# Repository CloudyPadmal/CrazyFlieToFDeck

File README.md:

# CrazyFlieToFDeck

This repository contains KiCAD source files and generated gerber files for **CrazyFlie Obstacle Avoidance Sensor Deck**.

<table>
<tr>
<th>Front View</td>
<th>Bottom View</td>
</tr>
<tr>
<td></td>
<td></td>
</tr>
</table>

## Time of Flight Sensor

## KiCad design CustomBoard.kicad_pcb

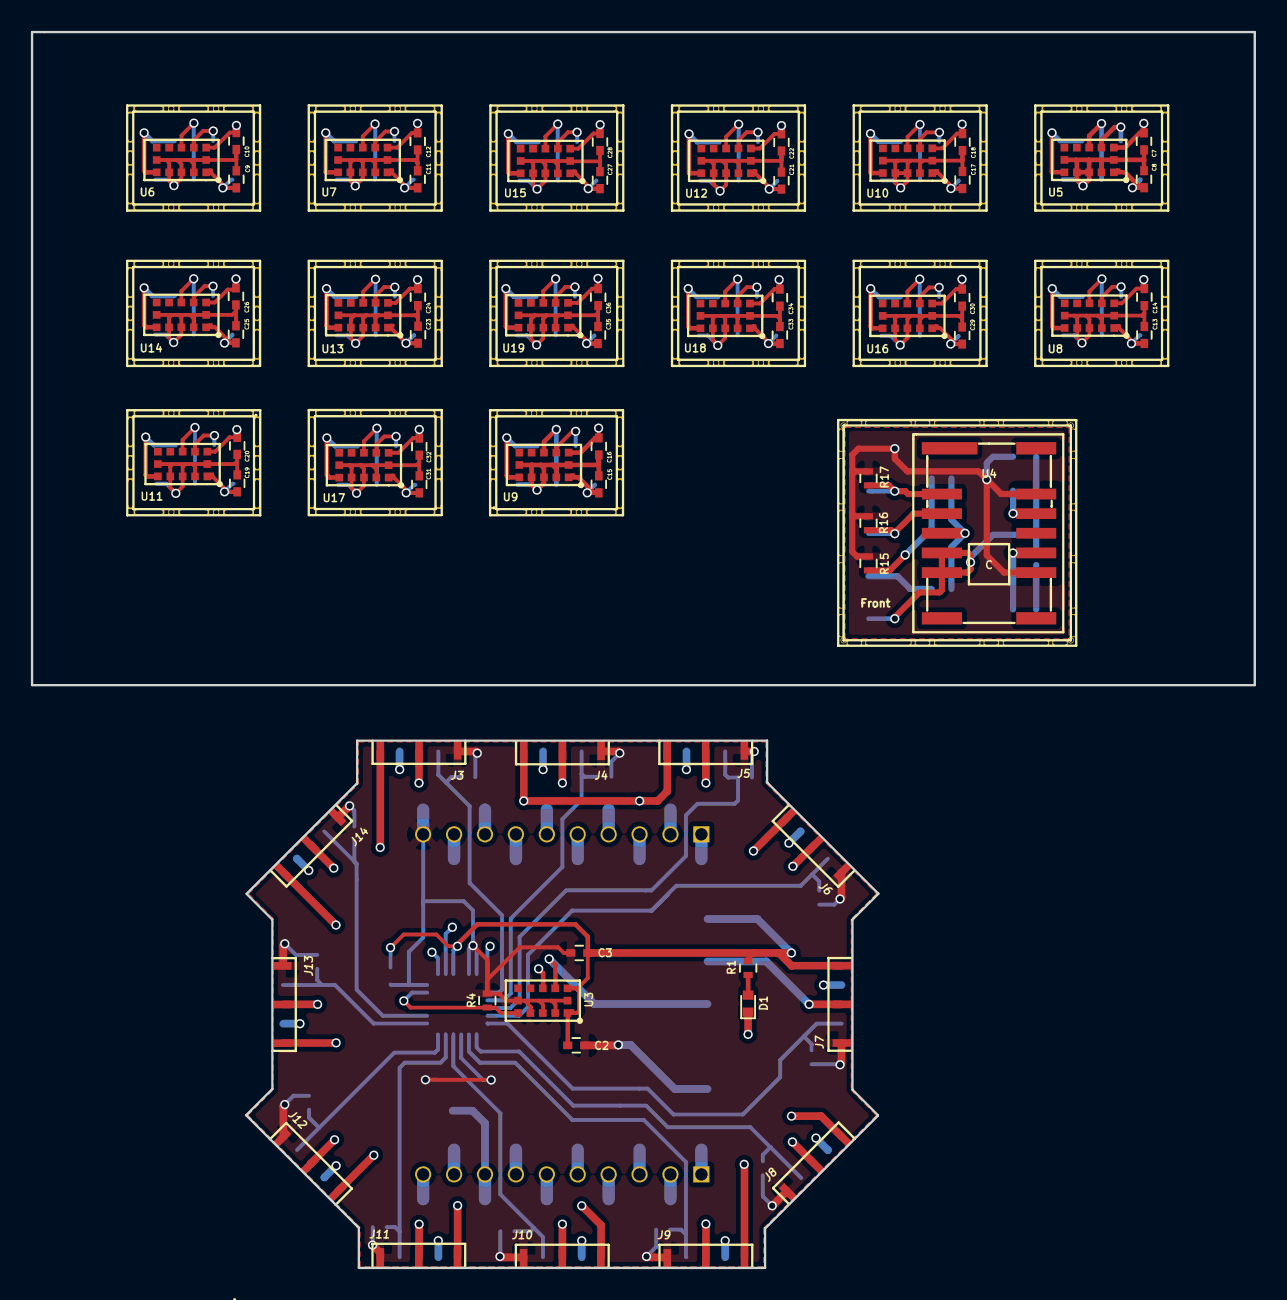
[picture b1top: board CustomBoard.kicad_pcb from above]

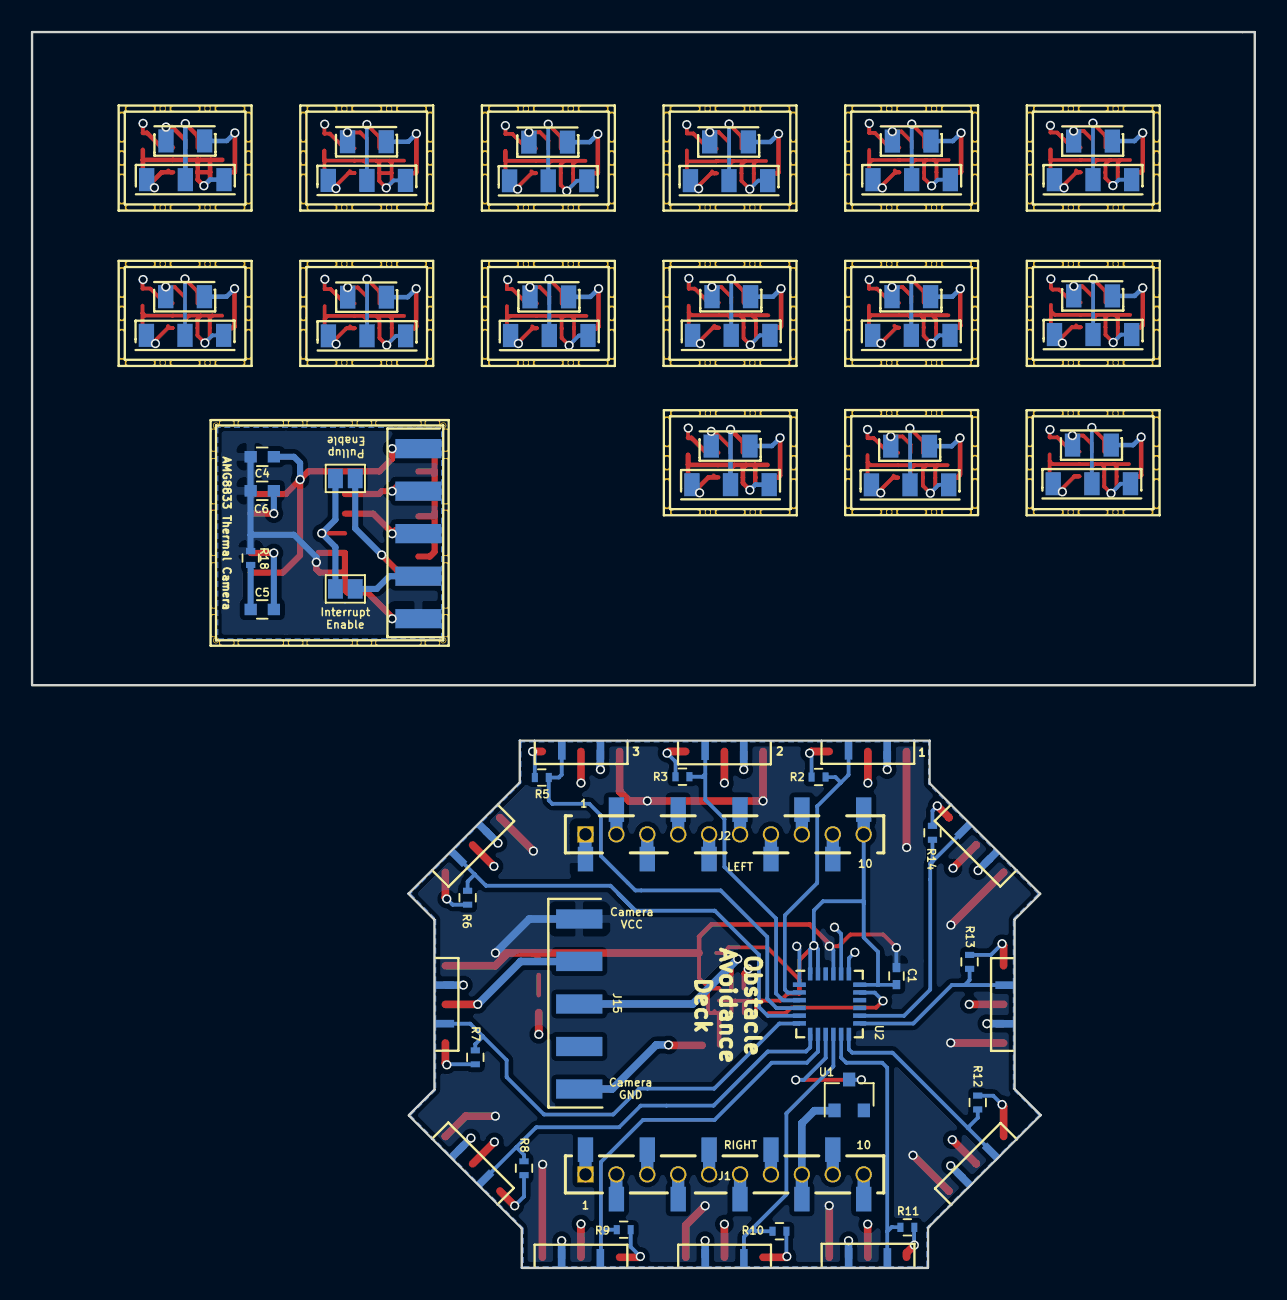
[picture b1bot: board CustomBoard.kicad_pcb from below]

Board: 4 copper layers, 79.1 x 79.9 mm, 122 parts (55 on the bottom side), 105 nets.

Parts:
C1, C2, C7, C9, C11, C13, C15, C17, C19, C21, C23, C25, C27, C29, C31, C33, C35: 100n; C_0402
C3, C8, C10, C12, C14, C16, C18, C20, C22, C24, C26, C28, C30, C32, C34, C36: 4.7u; C_0402
C4: 10u; C_0603
C5: 1u; C_0603
C6: 1.5u; C_0603
D1: POWER_LED; LED_0402
J1: RIGHT; BF090-10-X-B2
J2: LEFT; BF090-10-X-B2
J3: Sensor01; SensorPads
J4: Sensor02; SensorPads
J5: Sensor03; SensorPads
J6: Sensor04; SensorPads
J7: Sensor05; SensorPads
J8: Sensor06; SensorPads
J9: Sensor07; SensorPads
J10: Sensor08; SensorPads
J11: Sensor09; SensorPads
J12: Sensor10; SensorPads
J13: Sensor11; SensorPads
J14: Sensor12; SensorPads
J15, J18: Camera; AMGCam
J16: PulCon; GS2
J17: IntCon; GS2
J19, J21, J23, J25, J27, J29, J31, J33, J35, J37, J39, J41, J43, J45, J47: Top; ToFTop
J20, J22, J24, J26, J28, J30, J32, J34, J36, J38, J40, J42, J44, J46, J48: Bot; ToFBottom
R1: 2k; R_0402
R2, R3, R4, R5, R6, R7, R8, R9, R10, R11, R12, R13, R14, R15, R16, R17: 10k; R_0402
R18: 20R; R_0402
U1: DS28E05; SOT-23
U2: PCA9555; QFN-24_4x4mm_Pitch0.5mm
U3, U5, U6, U7, U8, U9, U10, U11, U12, U13, U14, U15, U16, U17, U18, U19: VL53L1X
U4: AMG8833

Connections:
GND: C1.2, C2.2, C3.2, J2.10, J3.1, J4.1, J5.1, J6.1, J7.1, J8.1, J9.1, J10.1, J11.1, J12.1, J13.1, J14.1, J15.1, R2.1, R3.1, R4.2, R5.1, R6.1, R7.1, R8.1, R9.1, R10.1, R11.1, R12.1, R13.1, R14.1, U1.3, U2.9, U2.18, U2.23, U2.24, U3.2, U3.3, U3.4, U3.6, U3.12
GNDCam: C4.2, C6.2, J18.1, R18.2, U4.5, U4.6
INTCam: J17.2, J18.2
unnamed: C5.1, U4.10
unnamed: C5.2, R18.1
unnamed: C6.1, U4.12
unnamed: C7.1, C8.1, J20.1, U5.1, U5.11
unnamed: C7.2, C8.2, J20.3, U5.2, U5.3, U5.4, U5.6, U5.12
unnamed: C9.1, C10.1, J22.1, U6.1, U6.11
unnamed: C9.2, C10.2, J22.3, U6.2, U6.3, U6.4, U6.6, U6.12
unnamed: C11.1, C12.1, J24.1, U7.1, U7.11
unnamed: C11.2, C12.2, J24.3, U7.2, U7.3, U7.4, U7.6, U7.12
unnamed: C13.1, C14.1, J26.1, U8.1, U8.11
unnamed: C13.2, C14.2, J26.3, U8.2, U8.3, U8.4, U8.6, U8.12
unnamed: C15.1, C16.1, J28.1, U9.1, U9.11
unnamed: C15.2, C16.2, J28.3, U9.2, U9.3, U9.4, U9.6, U9.12
unnamed: C17.1, C18.1, J30.1, U10.1, U10.11
unnamed: C17.2, C18.2, J30.3, U10.2, U10.3, U10.4, U10.6, U10.12
unnamed: C19.1, C20.1, J32.1, U11.1, U11.11
unnamed: C19.2, C20.2, J32.3, U11.2, U11.3, U11.4, U11.6, U11.12
unnamed: C21.1, C22.1, J34.1, U12.1, U12.11
unnamed: C21.2, C22.2, J34.3, U12.2, U12.3, U12.4, U12.6, U12.12
unnamed: C23.1, C24.1, J36.1, U13.1, U13.11
unnamed: C23.2, C24.2, J36.3, U13.2, U13.3, U13.4, U13.6, U13.12
unnamed: C25.1, C26.1, J38.1, U14.1, U14.11
unnamed: C25.2, C26.2, J38.3, U14.2, U14.3, U14.4, U14.6, U14.12
unnamed: C27.1, C28.1, J40.1, U15.1, U15.11
unnamed: C27.2, C28.2, J40.3, U15.2, U15.3, U15.4, U15.6, U15.12
unnamed: C29.1, C30.1, J42.1, U16.1, U16.11
unnamed: C29.2, C30.2, J42.3, U16.2, U16.3, U16.4, U16.6, U16.12
unnamed: C31.1, C32.1, J44.1, U17.1, U17.11
unnamed: C31.2, C32.2, J44.3, U17.2, U17.3, U17.4, U17.6, U17.12
unnamed: C33.1, C34.1, J46.1, U18.1, U18.11
unnamed: C33.2, C34.2, J46.3, U18.2, U18.3, U18.4, U18.6, U18.12
unnamed: C35.1, C36.1, J48.1, U19.1, U19.11
unnamed: C35.2, C36.2, J48.3, U19.2, U19.3, U19.4, U19.6, U19.12
unnamed: D1.1, U2.1
unnamed: D1.2, R1.2
unnamed: J16.1, R15.2
unnamed: J16.2, J17.1, U4.4
unnamed: J19.1, U5.10
unnamed: J19.2, U5.5
unnamed: J20.2, U5.9
unnamed: J21.1, U6.10
unnamed: J21.2, U6.5
unnamed: J22.2, U6.9
unnamed: J23.1, U7.10
unnamed: J23.2, U7.5
unnamed: J24.2, U7.9
unnamed: J25.1, U8.10
unnamed: J25.2, U8.5
unnamed: J26.2, U8.9
unnamed: J27.1, U9.10
unnamed: J27.2, U9.5
unnamed: J28.2, U9.9
unnamed: J29.1, U10.10
unnamed: J29.2, U10.5
unnamed: J30.2, U10.9
unnamed: J31.1, U11.10
unnamed: J31.2, U11.5
unnamed: J32.2, U11.9
unnamed: J33.1, U12.10
unnamed: J33.2, U12.5
unnamed: J34.2, U12.9
unnamed: J35.1, U13.10
unnamed: J35.2, U13.5
unnamed: J36.2, U13.9
unnamed: J37.1, U14.10
unnamed: J37.2, U14.5
unnamed: J38.2, U14.9
unnamed: J39.1, U15.10
unnamed: J39.2, U15.5
unnamed: J40.2, U15.9
unnamed: J41.1, U16.10
unnamed: J41.2, U16.5
unnamed: J42.2, U16.9
unnamed: J43.1, U17.10
unnamed: J43.2, U17.5
unnamed: J44.2, U17.9
unnamed: J45.1, U18.10
unnamed: J45.2, U18.5
unnamed: J46.2, U18.9
unnamed: J47.1, U19.10
unnamed: J47.2, U19.5
unnamed: J48.2, U19.9
OW: J1.8, U1.1
S01: J3.2, R2.2, U2.2
S02: J4.2, R3.2, U2.3
S03: J5.2, R5.2, U2.4
S04: J6.2, R6.2, U2.5
S05: J7.2, R7.2, U2.6
S06: J8.2, R8.2, U2.7
S07: J9.2, R9.2, U2.8
S08: J10.2, R10.2, U2.10
S09: J11.2, R11.2, U2.11
S10: J12.2, R12.2, U2.12
S11: J13.2, R13.2, U2.13
S12: J14.2, R14.2, U2.14
S15: R4.1, U2.17, U3.5
SCL: J2.5, J3.4, J4.4, J5.4, J6.4, J7.4, J8.4, J9.4, J10.4, J11.4, J12.4, J13.4, J14.4, J15.3, U2.19, U3.10
SCLCam: J18.3, R16.2, U4.3
SDA: J2.4, J3.3, J4.3, J5.3, J6.3, J7.3, J8.3, J9.3, J10.3, J11.3, J12.3, J13.3, J14.3, J15.4, U2.20, U3.9
SDACam: J18.4, R17.2, U4.2
VCC: C1.1, C2.1, C3.1, J2.1, J3.5, J4.5, J5.5, J6.5, J7.5, J8.5, J9.5, J10.5, J11.5, J12.5, J13.5, J14.5, J15.5, R1.1, U2.21, U3.1, U3.11
VCCCam: C4.1, J18.5, R15.1, R16.1, R17.1, U4.9, U4.13

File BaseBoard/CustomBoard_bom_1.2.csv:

Component,Description,Part,References,Value,Footprint,Quantity Per PCB,Datasheet
1,Unpolarized capacitor,C_Small,C1 C2,100n,C_0603,2,
2,Unpolarized capacitor,C_Small,C3,4.7u,C_0603,1,
3,"LED generic, alternativ symbol",LED_ALT,D1,POWER_LED,LED_0603,1,
4,"Generic connector, single row, 01x05",Conn_01x05,J15,Camera,AMGCam,1,
5,"Generic connector, single row, 01x10",Conn_01x10,J2,LEFT,BF090-10-X-B2,1,
6,"Generic connector, single row, 01x10",Conn_01x10,J1,RIGHT,BF090-10-X-B2,1,
7,"Generic connector, single row, 01x05",Conn_01x05,J3,Sensor01,SensorPads,1,
8,"Generic connector, single row, 01x05",Conn_01x05,J4,Sensor02,SensorPads,1,
9,"Generic connector, single row, 01x05",Conn_01x05,J5,Sensor03,SensorPads,1,
10,"Generic connector, single row, 01x05",Conn_01x05,J6,Sensor04,SensorPads,1,
11,"Generic connector, single row, 01x05",Conn_01x05,J7,Sensor05,SensorPads,1,
12,"Generic connector, single row, 01x05",Conn_01x05,J8,Sensor06,SensorPads,1,
13,"Generic connector, single row, 01x05",Conn_01x05,J9,Sensor07,SensorPads,1,
14,"Generic connector, single row, 01x05",Conn_01x05,J10,Sensor08,SensorPads,1,
15,"Generic connector, single row, 01x05",Conn_01x05,J11,Sensor09,SensorPads,1,
16,"Generic connector, single row, 01x05",Conn_01x05,J12,Sensor10,SensorPads,1,
17,"Generic connector, single row, 01x05",Conn_01x05,J13,Sensor11,SensorPads,1,
18,"Generic connector, single row, 01x05",Conn_01x05,J14,Sensor12,SensorPads,1,
19,Resistor,R,R2 R3 R4 R5 R6 R7 R8 R9 R10 R11 R12 R13 R14,10k,R_0603,13,
20,Resistor,R,R1,2k,R_0603,1,
21,,DS28E05,U1,DS28E05,SOT-23,1,
22,,PCA9555X,U2,PCA9555X,TSSOP-24_4.4x7.8mm_Pitch0.65mm,1,https://www.mouser.com/datasheet/2/302/PCA9555A-1127572.pdf
23,,VL53L1X,U3,VL53L1X,VL53L1X,1,





Component Groups:,23
Component Count:,36
Fitted Components:,36
Number of PCBs:,1
Total components:,36
Schematic Version:,1.2
Schematic Date:,2018-07-24
BoM Date:,Sat 11 Aug 2018 04:17:48 PM +0530
Schematic Source:,/home/knight/Documents/KiCAD/FinalBoards/CrazyFlieCustomBoardBase/CustomBoard.sch
KiCad Version:,Eeschema 4.0.7-e2-6376~58~ubuntu16.04.1

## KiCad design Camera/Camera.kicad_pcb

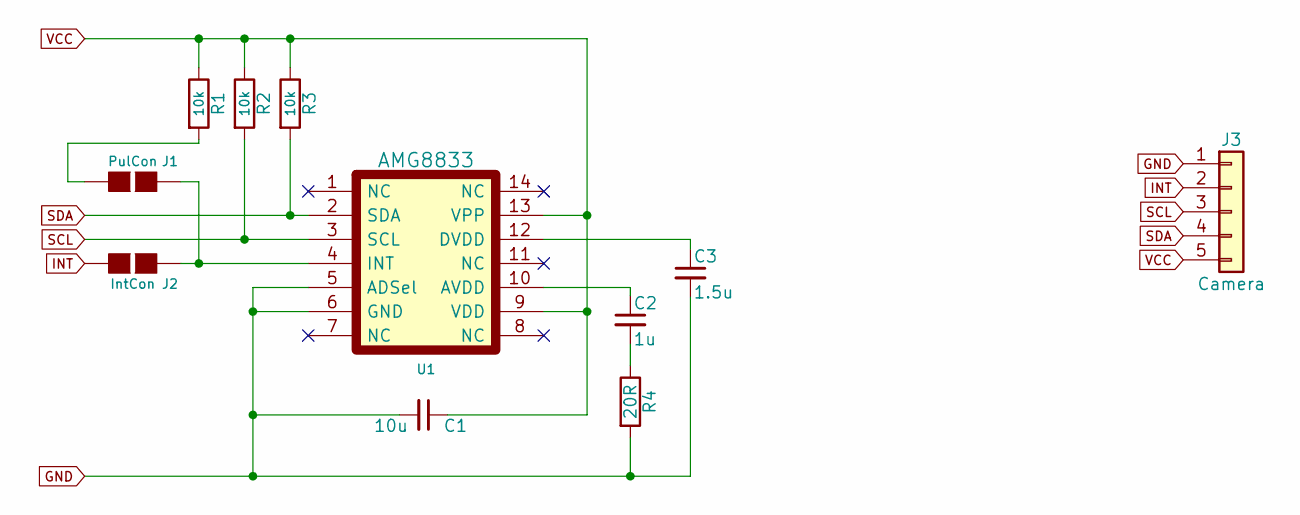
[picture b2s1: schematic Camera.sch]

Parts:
C1: 10u; C_0603
C2: 1u; C_0603
C3: 1.5u; C_0603
J1: PulCon; GS2
J2: IntCon; GS2
J3: Camera; AMGCam
R1, R2, R3: 10k; R_0402
R4: 20R; R_0402
U1: AMG8833

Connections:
GND: C1.2, C3.2, J3.1, R4.2, U1.5 (ADSel), U1.6 (GND)
INT: J2.2 (G2), J3.2
unnamed: C2.1, U1.10 (AVDD)
unnamed: C2.2, R4.1
unnamed: C3.1, U1.12 (DVDD)
unnamed: J1.1 (G1), R1.2
unnamed: J1.2 (G2), J2.1 (G1), U1.4 (INT)
SCL: J3.3, R2.2, U1.3 (SCL)
SDA: J3.4, R3.2, U1.2 (SDA)
VCC: C1.1, J3.5, R1.1, R2.1, R3.1, U1.9 (VDD), U1.13 (VPP)

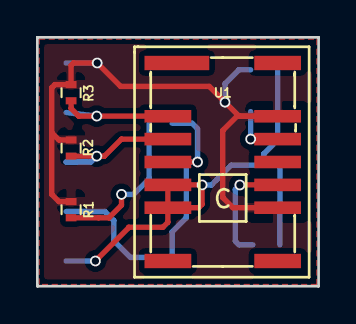
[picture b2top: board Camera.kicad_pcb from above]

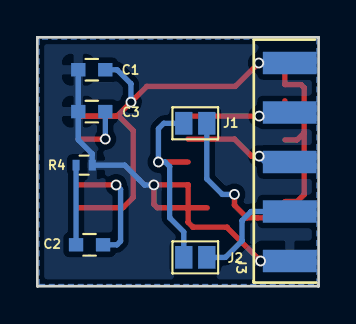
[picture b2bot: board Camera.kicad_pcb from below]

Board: 2 copper layers, 15.6 x 13.8 mm, 11 parts (7 on the bottom side), 10 nets.

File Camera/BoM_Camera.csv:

Component,Description,Part,References,Value,Footprint,Quantity Per PCB,Datasheet
1,Unpolarized capacitor,C_Small,C3,1.5u,C_0603,1,
2,Unpolarized capacitor,C_Small,C1,10u,C_0603,1,
3,Unpolarized capacitor,C_Small,C2,1u,C_0603,1,
7,Resistor,R,R1 R2 R3,10k,R_0402,3,
8,Resistor,R,R4,20R,R_0402,1,
9,Camera module,AMG8833,U1,AMG8833,AMG8833,1,
,,,,,,,
,,,,,,,
,,,,,,,
,,,,,,,
,,,,,,,
Component Groups:,9,,,,,,
Component Count:,11,,,,,,
Fitted Components:,11,,,,,,
Number of PCBs:,1,,,,,,
Total components:,11,,,,,,

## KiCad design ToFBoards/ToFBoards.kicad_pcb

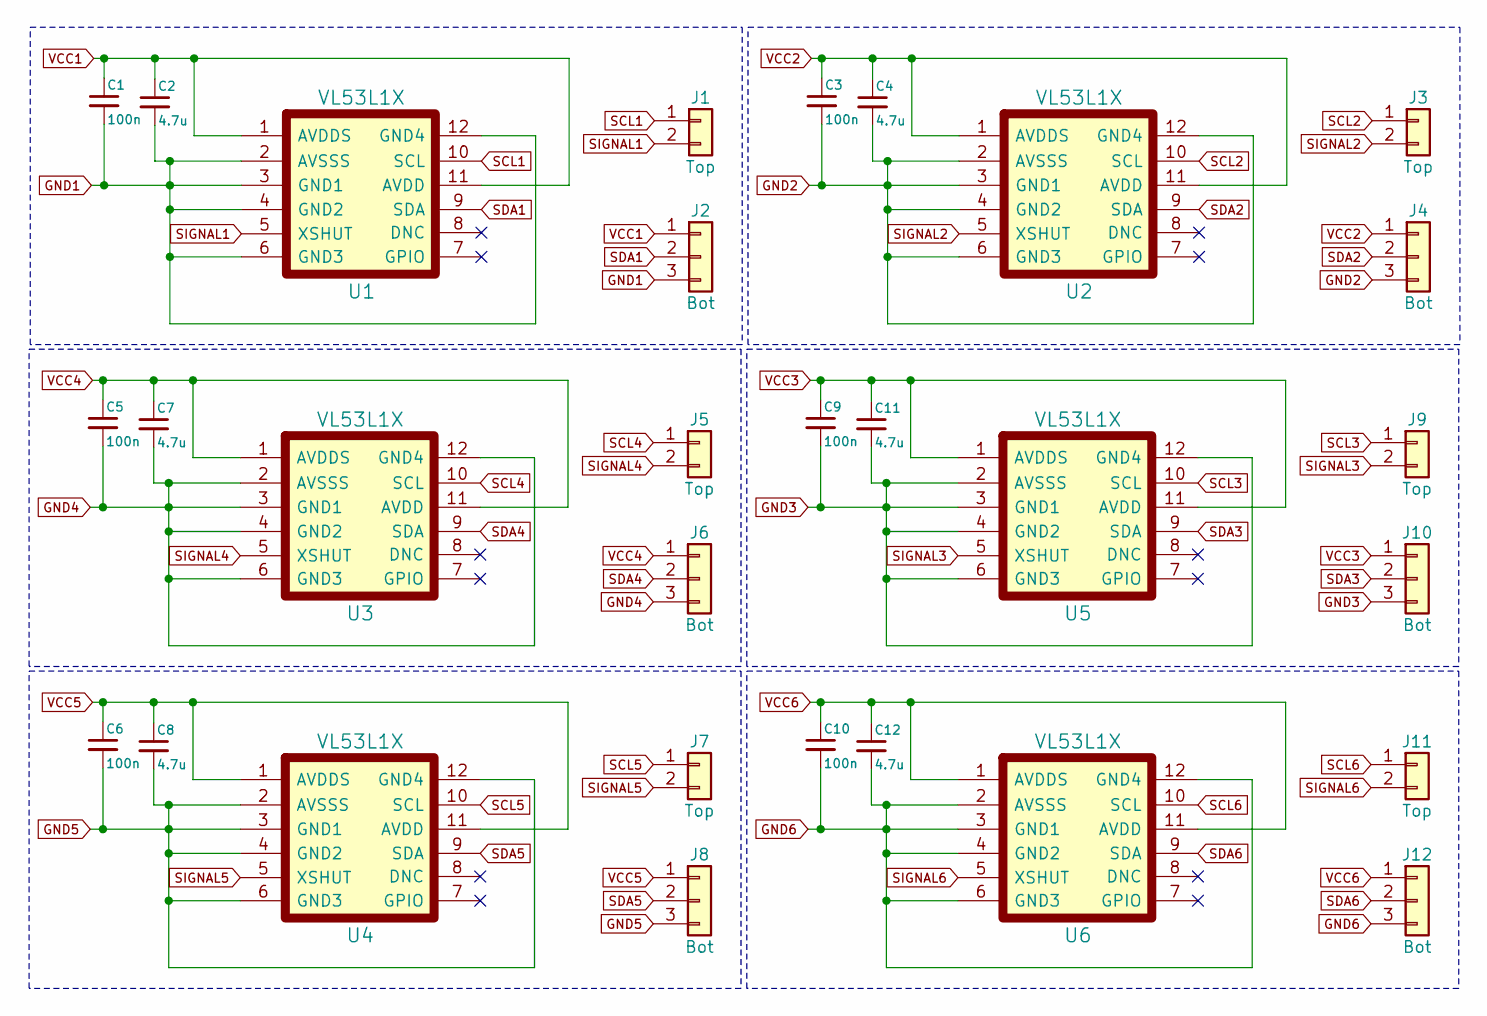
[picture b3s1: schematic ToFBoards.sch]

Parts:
C1, C3, C5, C6, C9, C10: 100n; C_0402
C2, C4, C7, C8, C11, C12: 4.7u; C_0402
J1, J3, J5, J7, J9, J11: Top; ToFTop
J2, J4, J6, J8, J10, J12: Bot; ToFBottom
U1, U2, U3, U4, U5, U6: VL53L1X

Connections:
GND1: C1.2, C2.2, J2.3, U1.2 (AVSSS), U1.3 (GND1), U1.4 (GND2), U1.6 (GND3), U1.12 (GND4)
GND2: C3.2, C4.2, J4.3, U2.2 (AVSSS), U2.3 (GND1), U2.4 (GND2), U2.6 (GND3), U2.12 (GND4)
GND3: C9.2, C11.2, J10.3, U5.2 (AVSSS), U5.3 (GND1), U5.4 (GND2), U5.6 (GND3), U5.12 (GND4)
GND4: C5.2, C7.2, J6.3, U3.2 (AVSSS), U3.3 (GND1), U3.4 (GND2), U3.6 (GND3), U3.12 (GND4)
GND5: C6.2, C8.2, J8.3, U4.2 (AVSSS), U4.3 (GND1), U4.4 (GND2), U4.6 (GND3), U4.12 (GND4)
GND6: C10.2, C12.2, J12.3, U6.2 (AVSSS), U6.3 (GND1), U6.4 (GND2), U6.6 (GND3), U6.12 (GND4)
SCL1: J1.1, U1.10 (SCL)
SCL2: J3.1, U2.10 (SCL)
SCL3: J9.1, U5.10 (SCL)
SCL4: J5.1, U3.10 (SCL)
SCL5: J7.1, U4.10 (SCL)
SCL6: J11.1, U6.10 (SCL)
SDA1: J2.2, U1.9 (SDA)
SDA2: J4.2, U2.9 (SDA)
SDA3: J10.2, U5.9 (SDA)
SDA4: J6.2, U3.9 (SDA)
SDA5: J8.2, U4.9 (SDA)
SDA6: J12.2, U6.9 (SDA)
SIGNAL1: J1.2, U1.5 (XSHUT)
SIGNAL2: J3.2, U2.5 (XSHUT)
SIGNAL3: J9.2, U5.5 (XSHUT)
SIGNAL4: J5.2, U3.5 (XSHUT)
SIGNAL5: J7.2, U4.5 (XSHUT)
SIGNAL6: J11.2, U6.5 (XSHUT)
VCC1: C1.1, C2.1, J2.1, U1.1 (AVDDS), U1.11 (AVDD)
VCC2: C3.1, C4.1, J4.1, U2.1 (AVDDS), U2.11 (AVDD)
VCC3: C9.1, C11.1, J10.1, U5.1 (AVDDS), U5.11 (AVDD)
VCC4: C5.1, C7.1, J6.1, U3.1 (AVDDS), U3.11 (AVDD)
VCC5: C6.1, C8.1, J8.1, U4.1 (AVDDS), U4.11 (AVDD)
VCC6: C10.1, C12.1, J12.1, U6.1 (AVDDS), U6.11 (AVDD)

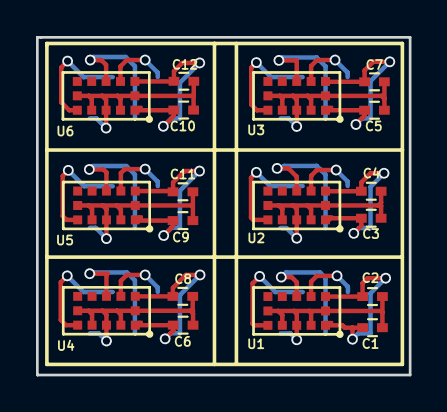
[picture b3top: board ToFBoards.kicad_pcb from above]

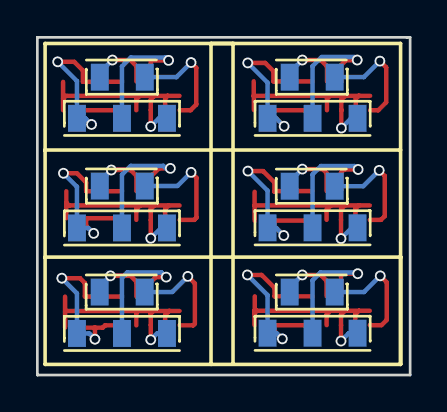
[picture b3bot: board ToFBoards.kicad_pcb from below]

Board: 2 copper layers, 20.7 x 18.8 mm, 30 parts (12 on the bottom side), 30 nets.

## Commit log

2018-07-24 datasheets and custom ICs
2018-07-24 added deck expanders
2018-07-25 pcb layout
2018-07-25 pcb layout update
2018-07-25 datasheet for slam deck
2018-07-25 4m range ToF sensor parts
2018-07-26 new footprints
2018-07-27 dimensions fixed
2018-07-27 routing started
2018-07-27 routing continues
2018-07-27 routing optimization
2018-07-28 modifications
2018-07-30 adding 4 layers
2018-07-30 routing power lines
2018-07-30 pull ups
2018-07-30 continue routing
2018-07-30 continue routing ..
2018-07-30 pads missing
2018-07-30 saved state
2018-07-31 footprints back
2018-07-31 footprints back all
2018-07-31 complete board
2018-07-31 ToF boards
2018-07-31 complete ToF boards
2018-07-31 fix commit issues
2018-07-31 camera module
2018-08-01 camera module pcb
2018-08-02 integrate cam module in main board
2018-08-02 reformatting
2018-08-02 gerber files
2018-08-03 ready
2018-08-03 update bom
2021-10-30 refactor: rearranged files into three folders
